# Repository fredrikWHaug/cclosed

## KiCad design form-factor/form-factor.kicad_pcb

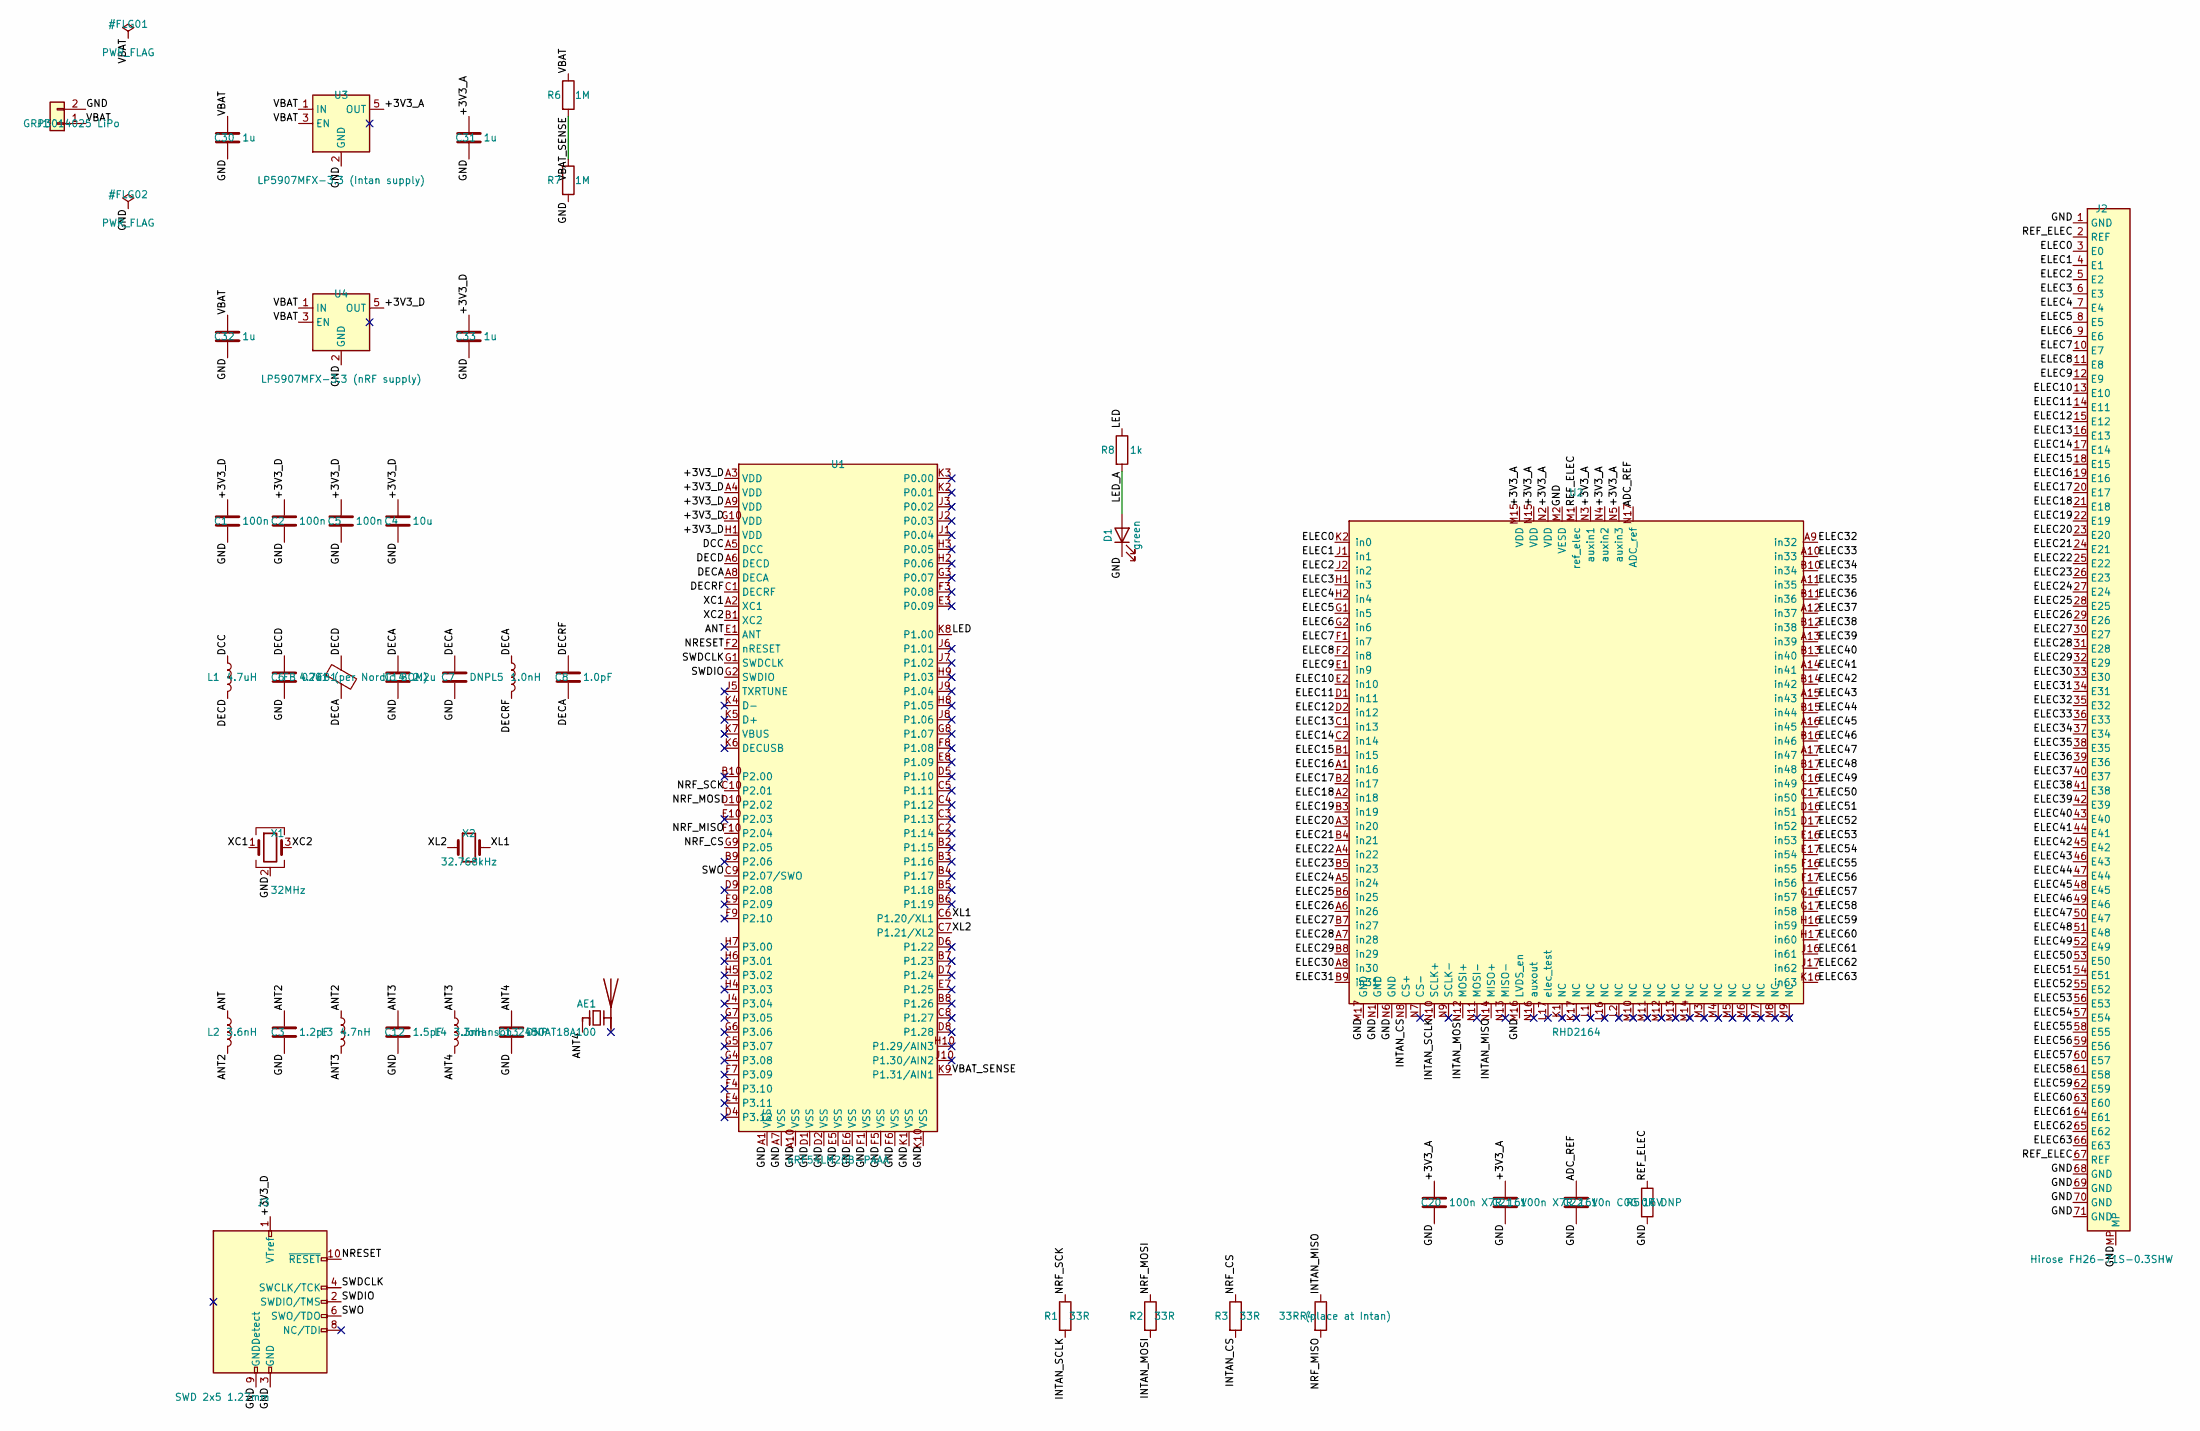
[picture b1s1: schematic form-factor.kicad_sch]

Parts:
AE1: Johanson 2450AT18A100; Johanson_2450AT18x100
C1, C2, C5: 100n; C_0201_0603Metric
C3: 1.2pF; C_0201_0603Metric
C4: 10u; C_0402_1005Metric
C6: 4.7u; C_0402_1005Metric
C7, C13: DNP; C_0201_0603Metric
C8: 1.0pF; C_0201_0603Metric
C12: 1.5pF; C_0201_0603Metric
C14: 2.2u; C_0201_0603Metric
C20, C21: 100n X7R 16V; C_0402_1005Metric
C22: 10n C0G 16V; C_0402_1005Metric
C30, C31, C32, C33: 1u; C_0402_1005Metric
D1: green; LED_0402_1005Metric
FB1: FB 0201 (per Nordic BOM); L_0201_0603Metric
J1: GRP3014025 LiPo; JST_SH_SM02B-SRSS-TB_1x02-1MP_P1.00mm_Horizontal
J2: Hirose FH26-71S-0.3SHW; Hirose_FH26-71S-0.3SHW_2Rows-71Pins-1MP_P0.60mm_Horizontal
J3: SWD 2x5 1.27mm; PinHeader_2x05_P1.27mm_Vertical_SMD
L1: 4.7uH; L_0603_1608Metric
L2: 3.6nH; L_0201_0603Metric
L3: 4.7nH; L_0201_0603Metric
L4: 3.3nH; L_0201_0603Metric
L5: 1.0nH; L_0201_0603Metric
R1, R2, R3: 33R; R_0402_1005Metric
R4: 33R (place at Intan); R_0402_1005Metric
R5: 0R DNP; R_0402_1005Metric
R6, R7: 1M; R_0402_1005Metric
R8: 1k; R_0402_1005Metric
U1: nRF54LM20B-PAAA; Nordic_CSP98_PAAA_3.67x3.85mm_P0.35mm
U2: RHD2164
U3: LP5907MFX-3.3 (Intan supply); SOT-23-5
U4: LP5907MFX-3.3 (nRF supply); SOT-23-5
X1: 32MHz; Crystal_SMD_2016-4Pin_2.0x1.6mm
X2: 32.768kHz; Crystal_SMD_2012-2Pin_2.0x1.2mm

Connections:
/+3V3_A: C20.1, C21.1, C31.1, U2.M15 (VDD), U2.N2 (VDD), U2.N3 (auxin1), U2.N4 (auxin2), U2.N5 (auxin3), U2.N15 (VDD), U3.5 (OUT)
/+3V3_D: C1.1, C2.1, C4.1, C5.1, C33.1, J3.1 (VCC), U1.A3 (VDD), U1.A4 (VDD), U1.A9 (VDD), U1.G10 (VDD), U1.H1 (VDD), U4.5 (OUT)
/ADC_REF: C22.1, U2.N17 (ADC_ref)
/ANT: L2.1, U1.E1 (ANT)
/ANT2: C3.1, L2.2, L3.1
/ANT3: C12.1, L3.2, L4.1
/ANT4: AE1.1 (FEED), C13.1, L4.2
/DCC: L1.1, U1.A5 (DCC)
/DECA: C7.1, C8.2, C14.1, FB1.2, L5.1, U1.A8 (DECA)
/DECD: C6.1, FB1.1, L1.2, U1.A6 (DECD)
/DECRF: C8.1, L5.2, U1.C1 (DECRF)
/ELEC0: J2.3 (E0), U2.K2 (in0)
/ELEC1: J2.4 (E1), U2.J1 (in1)
/ELEC2: J2.5 (E2), U2.J2 (in2)
/ELEC3: J2.6 (E3), U2.H1 (in3)
/ELEC4: J2.7 (E4), U2.H2 (in4)
/ELEC5: J2.8 (E5), U2.G1 (in5)
/ELEC6: J2.9 (E6), U2.G2 (in6)
/ELEC7: J2.10 (E7), U2.F1 (in7)
/ELEC8: J2.11 (E8), U2.F2 (in8)
/ELEC9: J2.12 (E9), U2.E1 (in9)
/ELEC10: J2.13 (E10), U2.E2 (in10)
/ELEC11: J2.14 (E11), U2.D1 (in11)
/ELEC12: J2.15 (E12), U2.D2 (in12)
/ELEC13: J2.16 (E13), U2.C1 (in13)
/ELEC14: J2.17 (E14), U2.C2 (in14)
/ELEC15: J2.18 (E15), U2.B1 (in15)
/ELEC16: J2.19 (E16), U2.A1 (in16)
/ELEC17: J2.20 (E17), U2.B2 (in17)
/ELEC18: J2.21 (E18), U2.A2 (in18)
/ELEC19: J2.22 (E19), U2.B3 (in19)
/ELEC20: J2.23 (E20), U2.A3 (in20)
/ELEC21: J2.24 (E21), U2.B4 (in21)
/ELEC22: J2.25 (E22), U2.A4 (in22)
/ELEC23: J2.26 (E23), U2.B5 (in23)
/ELEC24: J2.27 (E24), U2.A5 (in24)
/ELEC25: J2.28 (E25), U2.B6 (in25)
/ELEC26: J2.29 (E26), U2.A6 (in26)
/ELEC27: J2.30 (E27), U2.B7 (in27)
/ELEC28: J2.31 (E28), U2.A7 (in28)
/ELEC29: J2.32 (E29), U2.B8 (in29)
/ELEC30: J2.33 (E30), U2.A8 (in30)
/ELEC31: J2.34 (E31), U2.B9 (in31)
/ELEC32: J2.35 (E32), U2.A9 (in32)
/ELEC33: J2.36 (E33), U2.A10 (in33)
/ELEC34: J2.37 (E34), U2.B10 (in34)
/ELEC35: J2.38 (E35), U2.A11 (in35)
/ELEC36: J2.39 (E36), U2.B11 (in36)
/ELEC37: J2.40 (E37), U2.A12 (in37)
/ELEC38: J2.41 (E38), U2.B12 (in38)
/ELEC39: J2.42 (E39), U2.A13 (in39)
/ELEC40: J2.43 (E40), U2.B13 (in40)
/ELEC41: J2.44 (E41), U2.A14 (in41)
/ELEC42: J2.45 (E42), U2.B14 (in42)
/ELEC43: J2.46 (E43), U2.A15 (in43)
/ELEC44: J2.47 (E44), U2.B15 (in44)
/ELEC45: J2.48 (E45), U2.A16 (in45)
/ELEC46: J2.49 (E46), U2.B16 (in46)
/ELEC47: J2.50 (E47), U2.A17 (in47)
/ELEC48: J2.51 (E48), U2.B17 (in48)
/ELEC49: J2.52 (E49), U2.C16 (in49)
/ELEC50: J2.53 (E50), U2.C17 (in50)
/ELEC51: J2.54 (E51), U2.D16 (in51)
/ELEC52: J2.55 (E52), U2.D17 (in52)
/ELEC53: J2.56 (E53), U2.E16 (in53)
/ELEC54: J2.57 (E54), U2.E17 (in54)
/ELEC55: J2.58 (E55), U2.F16 (in55)
/ELEC56: J2.59 (E56), U2.F17 (in56)
/ELEC57: J2.60 (E57), U2.G16 (in57)
/ELEC58: J2.61 (E58), U2.G17 (in58)
/ELEC59: J2.62 (E59), U2.H16 (in59)
/ELEC60: J2.63 (E60), U2.H17 (in60)
/ELEC61: J2.64 (E61), U2.J16 (in61)
/ELEC62: J2.65 (E62), U2.J17 (in62)
/ELEC63: J2.66 (E63), U2.K16 (in63)
/INTAN_CS: R3.2, U2.N8 (CS+)
/INTAN_MISO: R4.1, U2.N14 (MISO+)
/INTAN_MOSI: R2.2, U2.N12 (MOSI+)
/INTAN_SCLK: R1.2, U2.N10 (SCLK+)
/LED: R8.1, U1.K8 (P1.00)
/LED_A: D1.2 (A), R8.2
/NRF_CS: R3.1, U1.G9 (P2.05)
/NRF_MISO: R4.2, U1.F10 (P2.04)
/NRF_MOSI: R2.1, U1.D10 (P2.02)
/NRF_SCK: R1.1, U1.C10 (P2.01)
/REF_ELEC: J2.2 (REF), J2.67 (REF), R5.1, U2.M1 (ref_elec)
/SWDCLK: J3.4 (SWCLK), U1.G1 (SWDCLK)
/SWDIO: J3.2 (SWDIO), U1.G2 (SWDIO)
/SWO: J3.6 (SWO), U1.C9 (P2.07/SWO)
/VBAT: C30.1, C32.1, J1.1, R6.1, U3.1 (IN), U3.3 (EN), U4.1 (IN), U4.3 (EN)
/VBAT_SENSE: R6.2, R7.1, U1.K9 (P1.31/AIN1)
/XC1: U1.A2 (XC1), X1.1
/XC2: U1.B1 (XC2), X1.3
/XL1: U1.C6 (P1.20/XL1), X2.2
/XL2: U1.C7 (P1.21/XL2), X2.1

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
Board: 2 copper layers, 43 parts (0 on the bottom side), 97 nets, no tracks yet.
